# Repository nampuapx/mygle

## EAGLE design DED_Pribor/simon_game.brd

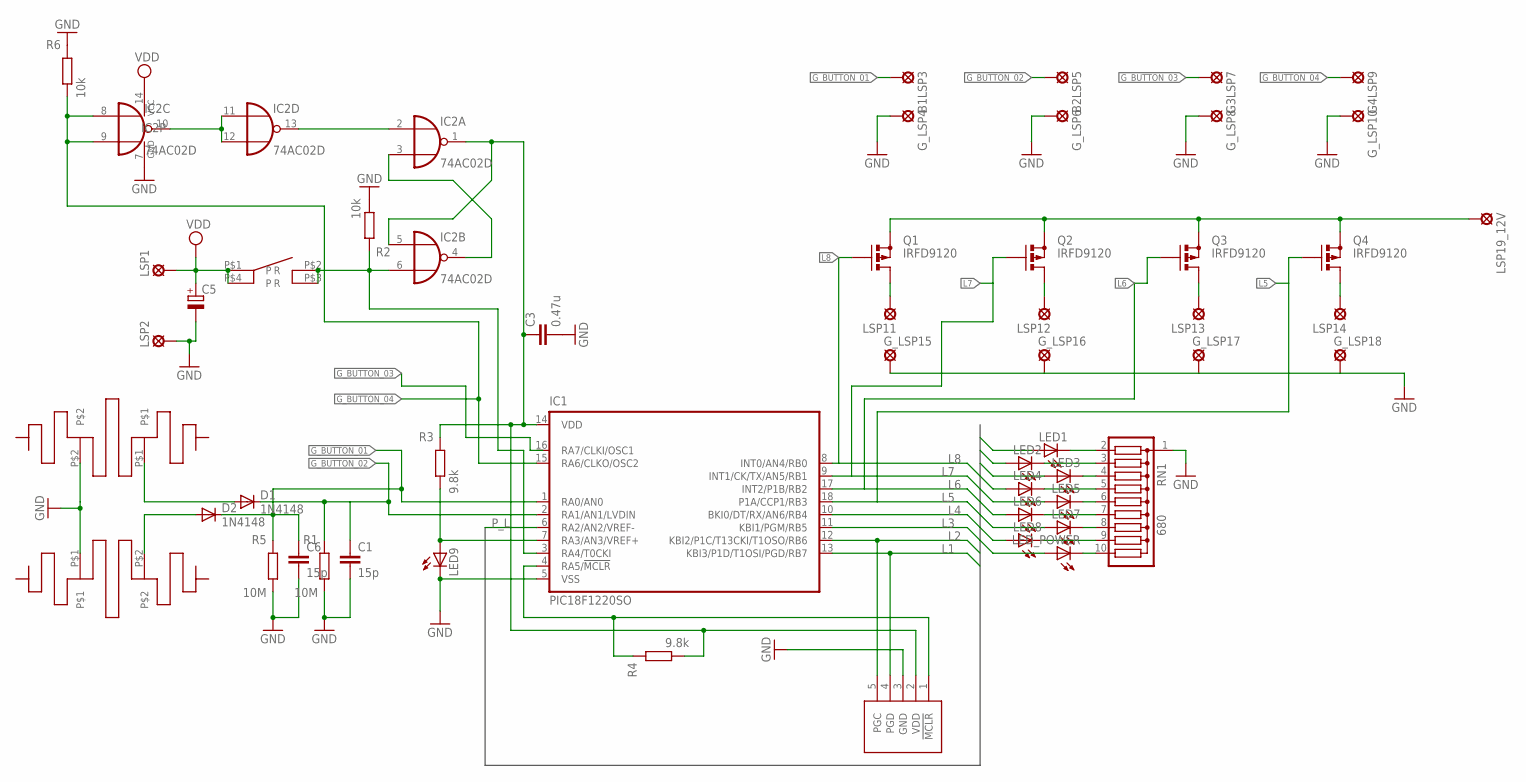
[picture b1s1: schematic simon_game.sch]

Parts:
B1LSP3, B2LSP5: SE14
C1, C6: 15p; C1206
C3: 0.47u; C1206
C5: CPOL-EUSMCA; SMC_A
D1, D2: 1N4148; DO35-10
G3LSP7, G4LSP9: SE14
G_LSP4, G_LSP6, G_LSP8, G_LSP10, G_LSP15, G_LSP16, G_LSP17, G_LSP18: SE14
IC1: PIC18F1220SO; SO-18W
IC2: 74AC02D; SO14
LED1, LED2, LED3, LED4, LED5, LED6, LED7, LED8: LED3MM
LED9: LED5MM
LED_POWER: LED3MM
LSP1, LSP2, LSP11, LSP12, LSP13, LSP14, LSP19_12V: SE14
Q1, Q2, Q3, Q4: IRFD9120; C370-01
R1, R5: 10M; M1206
R2, R6: 10k; M1206
R3, R4: 9.8k; M1206
RN1: 680; SIL10
U$1: TIKBUTTON01
U$2, U$3: ANTENNA; ANT!
U$4: PIC-PROG-CON

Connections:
GND: C1.2, C3.2, C5.-, C6.2, G_LSP4.MP, G_LSP6.MP, G_LSP8.MP, G_LSP10.MP, G_LSP15.MP, G_LSP16.MP, G_LSP17.MP, G_LSP18.MP, IC1.5 (VSS), IC2.7 (GND), LED9.K (C), LSP2.MP, R1.1, R2.1, R5.1, R6.2, RN1.1, U$2.P$1, U$3.P$2, U$4.3 (GND)
G_BUTTON_01: B1LSP3.MP, C6.1, D2.C, IC1.1 (RA0/AN0), R5.2
G_BUTTON_02: B2LSP5.MP, C1.1, D1.C, IC1.2 (RA1/AN1/LVDIN), R1.2
G_BUTTON_03: G3LSP7.MP
G_BUTTON_04: G4LSP9.MP, IC1.15 (RA6/CLKO/OSC2), IC2.8 (I0), IC2.9 (I1), R6.1
L1: IC1.13 (KBI3/P1D/T1OSI/PGD/RB7), LED1.A, U$4.4 (PGD)
L2: IC1.12 (KBI2/P1C/T13CKI/T1OSO/RB6), LED2.A, U$4.5 (PGC)
L3: IC1.11 (KBI1/PGM/RB5), LED3.A
L4: IC1.10 (BKI0/DT/RX/AN6/RB4), LED4.A
L5: IC1.18 (P1A/CCP1/RB3), LED5.A, Q4.G
L6: IC1.17 (INT2/P1B/RB2), LED6.A, Q3.G
L7: IC1.9 (INT1/CK/TX/AN5/RB1), LED7.A, Q2.G
L8: IC1.8 (INT0/AN4/RB0), LED8.A, Q1.G
unnamed: LSP19_12V.MP, Q1.S, Q2.S, Q3.S, Q4.S
unnamed: LED1.K (C), RN1.2
unnamed: LED2.K (C), RN1.3
unnamed: LED3.K (C), RN1.4
unnamed: LED4.K (C), RN1.5
unnamed: LED5.K (C), RN1.6
unnamed: LED6.K (C), RN1.7
unnamed: LED7.K (C), RN1.8
unnamed: LED8.K (C), RN1.9
unnamed: LED_POWER.K (C), RN1.10
unnamed: C3.1, IC1.14 (VDD), IC2.1 (O), IC2.5 (I0), R3.2, R4.1, U$4.2 (VDD)
unnamed: IC2.3 (I1), IC2.4 (O)
unnamed: D1.A, U$3.P$1
unnamed: IC2.2 (I0), IC2.13 (O)
unnamed: IC1.3 (RA4/T0CKI), IC2.6 (I1), R2.2, U$1.P$2 (R), U$1.P$3 (R)
unnamed: D2.A, U$2.P$2
unnamed: IC1.7 (RA3/AN3/VREF+), LED9.A, R3.1
unnamed: IC2.10 (O), IC2.11 (I0), IC2.12 (I1)
unnamed: LSP11.MP, Q1.D, Q1.D1 (D)
unnamed: IC1.4 (RA5/!MCLR), R4.2, U$4.1 (!MCLR)
unnamed: LSP12.MP, Q2.D, Q2.D1 (D)
unnamed: LSP13.MP, Q3.D, Q3.D1 (D)
unnamed: LSP14.MP, Q4.D, Q4.D1 (D)
P_L: IC1.6 (RA2/AN2/VREF-), LED_POWER.A
VDD: C5.+, IC2.14 (VCC), LSP1.MP, U$1.P$1, U$1.P$4

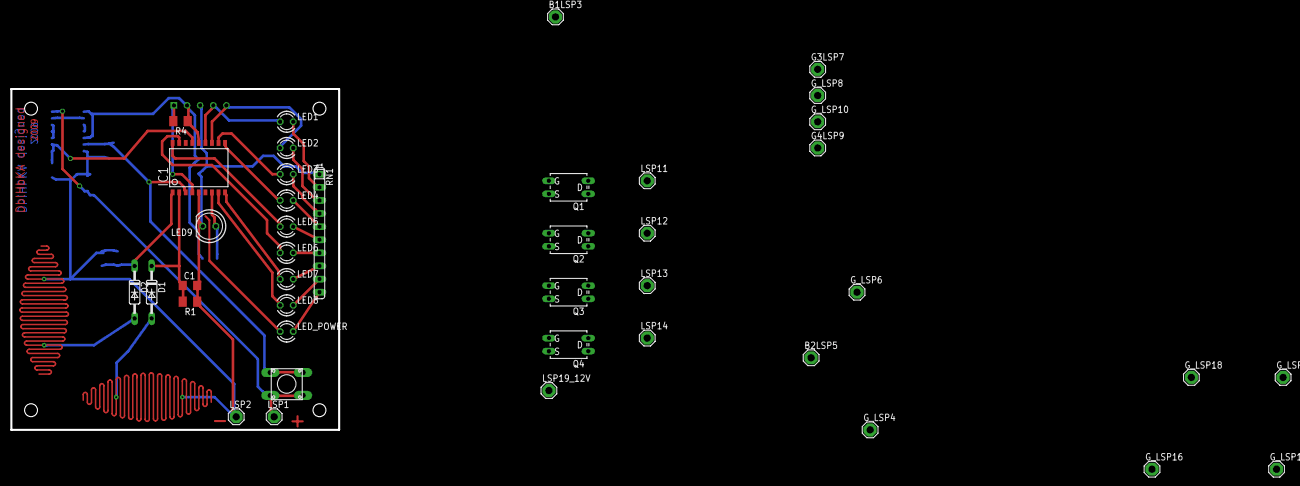
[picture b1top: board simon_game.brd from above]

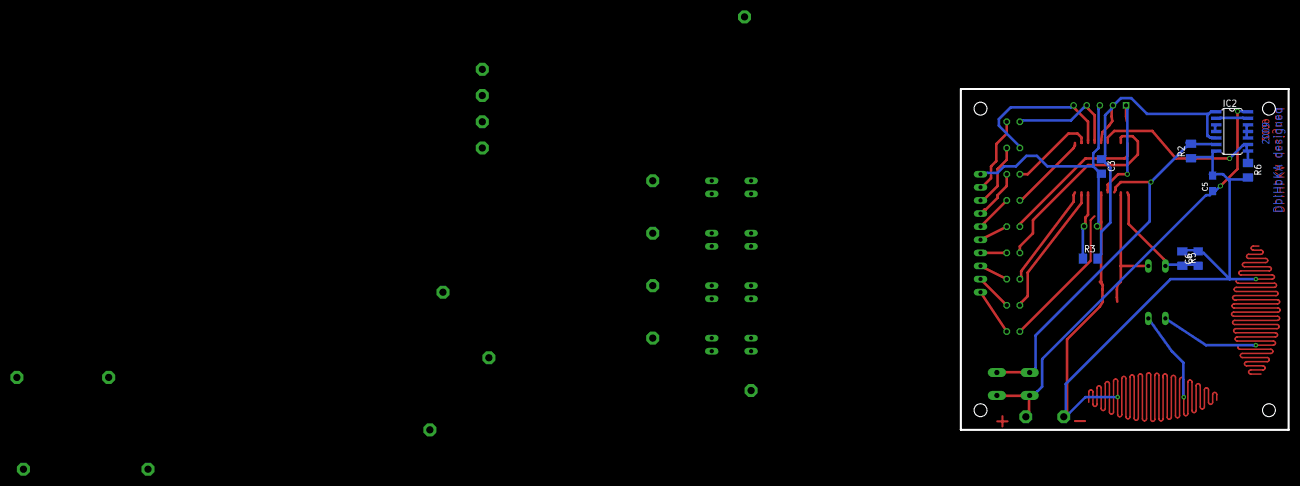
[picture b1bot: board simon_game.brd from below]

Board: 2 copper layers, 63.5 x 66.0 mm, 52 parts (8 on the bottom side), 37 nets.
